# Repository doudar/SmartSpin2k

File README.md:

# You can visit us at [Facebook](https://www.facebook.com/groups/716297469953492/)
# Did you know there's a SmartSpin2k companion App?

Find the source code here! -> [SS2kConfigApp](https://github.com/doudar/SS2kConfigApp/tree/develop) 

You can get it from the Apple App Store here:
<div style="display: flex; flex-wrap: wrap;">

</div>

Or for Android devices: 
<div style="display: flex; flex-wrap: wrap;">

</div>

# About
SmartSpin2k is a DIY project that allows you to turn any spin bike into a smart trainer. With SmartSpin2k, you can connect your spin bike to Zwift, TrainerRoad, or other popular training apps. This allows you to control your bike's resistance automatically, track your performance, and compete with other riders online.

SmartSpin2k is easy to build and requires only a few simple tools. The [entire build process](https://github.com/doudar/SS2k-Hardware/blob/main/SS2kR3BuildingInstructions.pdf) can be completed in under an hour.

If you are looking for a way to turn your spin bike into a smart trainer, SmartSpin2k is the perfect solution. With its new features and improvements, SmartSpin2k rev 3 is the best version yet.

## Getting Started

To get started with SmartSpin2k, you will need the following:

* A spin bike with a resistance control knob.
* A 3D printer.
* A soldering iron and basic soldering skills.

Once you have these materials, you can follow the [these instructions](https://github.com/doudar/SS2k-Hardware/blob/main/SS2kR3BuildingInstructions.pdf) to build your own SmartSpin2k. If you'd prefer to buy a pre-assembled kit, we have them for sale at [SmartSpin2k.com](https://www.smartspin2k.com/purchase-kits) 

## Features

SmartSpin2k offers a number of features, including:

* Automatic incline resistance control: SmartSpin2k can automatically control your bike's resistance based on the resistance settings in your training app. This allows you to focus on your workout and not worry about adjusting the resistance yourself.
* SmartSpin2k ERG function is a great way to improve your cycling performance. It allows you to train at a consistent power output, which is essential for improving your speed and endurance. ERG stands for "electronic resistance control." It works by automatically adjusting the resistance on your bike based on the power output you set in your training app.
* Online competition: SmartSpin2k can connect to Zwift, TrainerRoad, and many other cycling apps allowing you to compete with other riders online. This is a great way to stay motivated and push yourself to new heights.
* Do you have a spin bike that doesn't output realistic or accurate power numbers? If so, you're not alone. Many spin bikes have inaccurate power meters that can make it difficult to track your progress and train effectively. With SmartSpin2k you can calibrate the power output of your spin bike. 

## Conclusion

SmartSpin2k is a great way to turn any spin bike into a smart trainer. With its new features and improvements, SmartSpin2k Rev 3 is the best version yet. If you are looking for a way to improve your indoor cycling experience, SmartSpin2k is the perfect solution.

### Documentation
Everything you need to know is in the [SS2K Wiki](https://github.com/doudar/SmartSpin2k/wiki)
Hardware files and build assets are in [SS2k-Hardware](https://github.com/doudar/SS2k-Hardware).

## Contributing
1. Install Microsoft Visual Code. https://code.visualstudio.com/
2. Install the **pioarduino IDE** extension (`pioarduino.pioarduino-ide`) recommended by this repository in Visual Studio Code.
3. Install Python https://www.python.org/downloads/
4. Install Pre-commit. https://pre-commit.com `py -m pip install pre-commit`
5. Follow any install warnings to add pre-commit to your path. 
6. Install pre-push git hooks: `pre-commit install --hook-type pre-push`
7. Open this project in the pioarduino IDE.

For command-line builds, use a Python virtual environment and run `python -m pip install -r requirements-ci.txt` from the repository root to install the same pinned pioarduino Core used by CI. CI uses Python 3.11. If that environment already has the upstream `platformio` package installed, uninstall it before installing pioarduino; the two packages share Python modules and command names.

pioarduino still uses `platformio.ini`, the `.platformio` tool directory, and the `pio` / `platformio` commands. Build with `pio run -e release` (classic ESP32) or `pio run -e S3release` (ESP32-S3), and run native tests with `pio test -e native`. See [AGENTS.md](AGENTS.md) for build and validation details.

## Important announcement for existing users
If you experience an issue after upgrading firmware, please follow these instructions in the Wiki. Flashing instructions are available [HERE.](https://github.com/doudar/SmartSpin2k/wiki/Loading-Software)

## Licensing
The hardware designs are licensed under the [CERN Open Hardware License Version 2 - Permissive license](https://github.com/doudar/SS2k-Hardware/blob/main/Hardware/LICENSE).
The software in this project is licensed under the [GNU GENERAL PUBLIC LICENSE Version 2, June 1991 license](LICENSE).

[_^^@eMadman's IC4 model_](https://github.com/doudar/SS2k-Hardware/tree/main/Hardware/V2%20-%20Through%20Hole/Direct%20Mount)

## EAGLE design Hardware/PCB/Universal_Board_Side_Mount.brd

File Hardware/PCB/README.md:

PCB files. 

You'll only need these files if you want to customize the PCB or fab it someplace other than pcbway. 

To order directly from PCBway use this link : https://www.pcbway.com/project/shareproject/SmartSpin2k_PCB.html

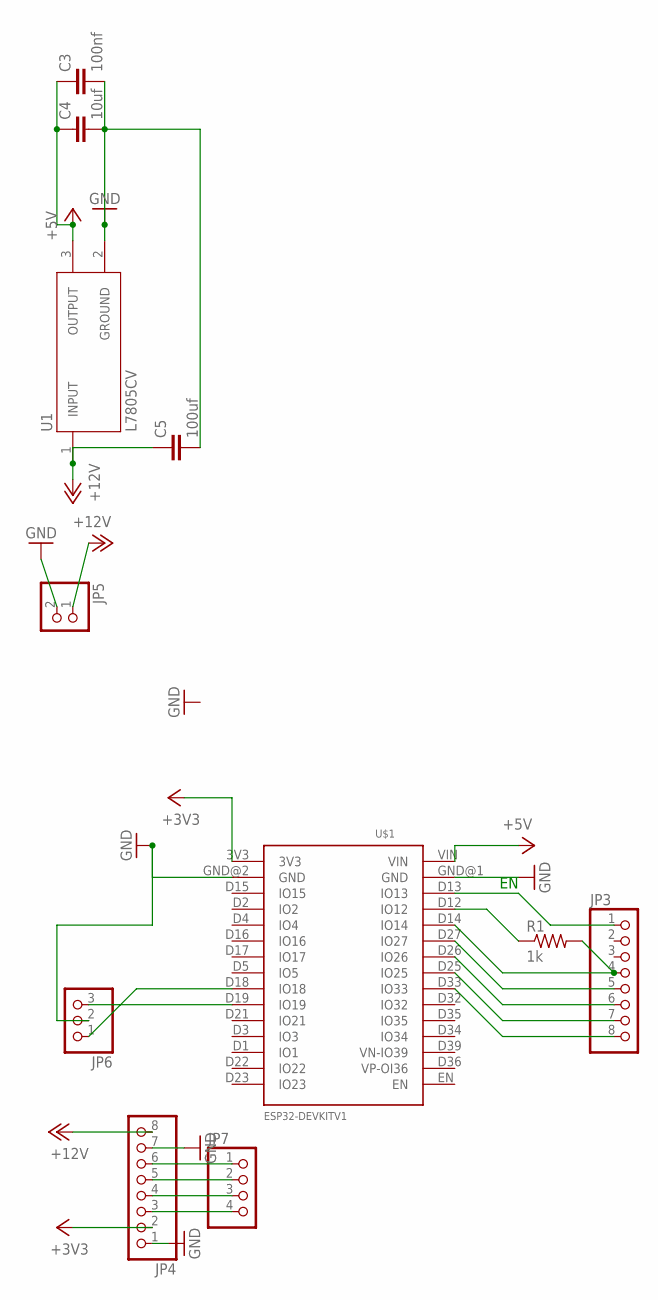
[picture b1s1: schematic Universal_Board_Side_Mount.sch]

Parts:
C3: 100nf; C2.5-3
C4: 10uf; C2.5-3
C5: 100uf; C2.5-3
JP3, JP4: PINHD-1X8; 1X08
JP5: PINHD-1X2; 1X02
JP6: PINHD-1X3; 1X03
JP7: PINHD-1X4; 1X04
R1: 1k; 0204/7
U1: L7805CV; TO255P1040X460X1968-3
U$1: ESP32DEVKITV1; ESP32-DEVKITV1

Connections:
+3V3: JP4.2, U$1.3V3
+5V: C3.1, C4.1, U1.3 (OUTPUT), U$1.VIN
+12V: C5.1, JP4.8, JP5.1, U1.1 (INPUT)
GND: C3.2, C4.2, C5.2, JP4.1, JP4.7, JP5.2, JP6.2, U1.2 (GROUND), U$1.GND@1 (GND), U$1.GND@2 (GND)
unnamed: JP3.4, R1.2, U$1.D14 (IO14)
unnamed: JP3.1, U$1.D13 (IO13)
unnamed: R1.1, U$1.D12 (IO12)
unnamed: JP3.5, U$1.D27 (IO27)
unnamed: JP3.6, U$1.D26 (IO26)
unnamed: JP3.7, U$1.D25 (IO25)
unnamed: JP3.8, U$1.D33 (IO33)
unnamed: JP4.6, JP7.1
unnamed: JP4.5, JP7.2
unnamed: JP4.4, JP7.3
unnamed: JP4.3, JP7.4
unnamed: JP6.3, U$1.D19 (IO19)
unnamed: JP6.1, U$1.D18 (IO18)

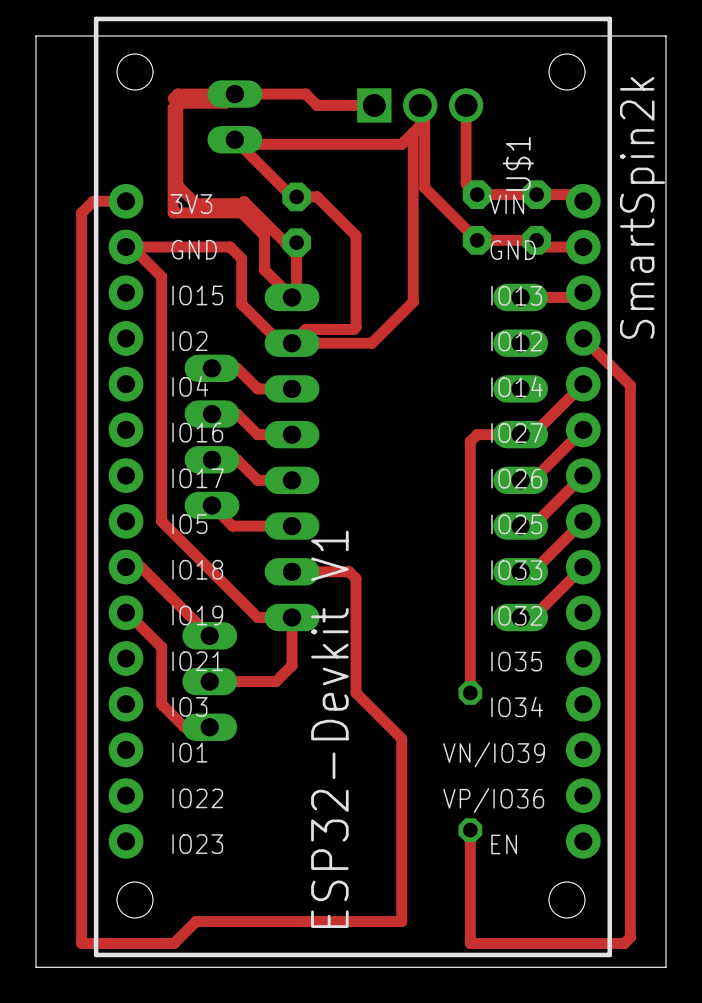
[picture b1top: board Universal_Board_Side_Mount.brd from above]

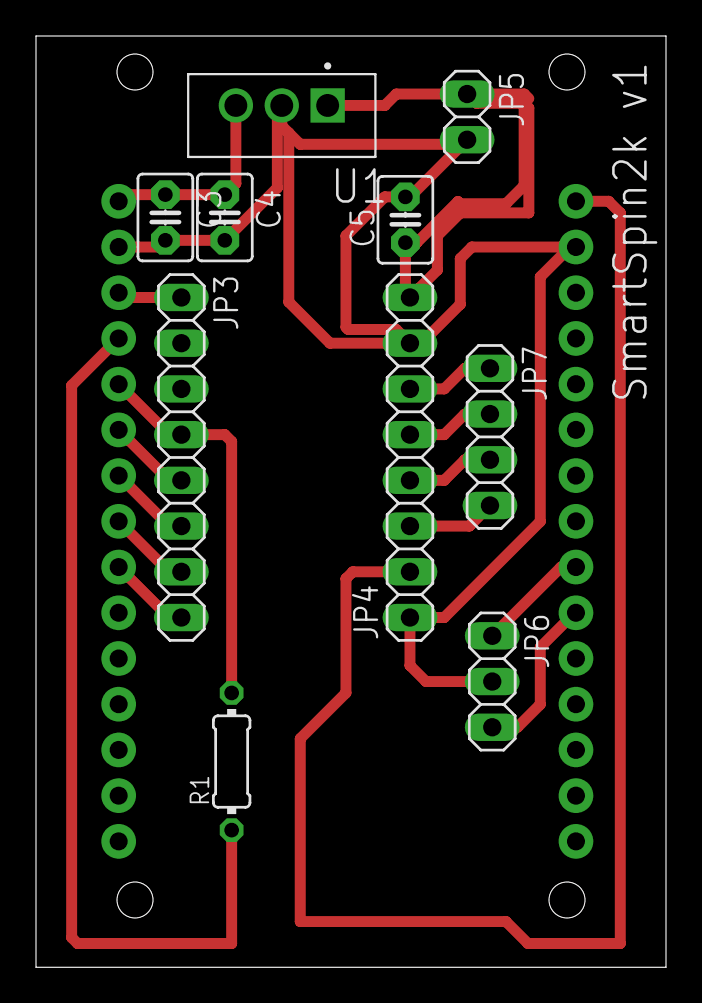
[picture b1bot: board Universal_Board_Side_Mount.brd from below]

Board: 2 copper layers, 35.0 x 51.7 mm, 11 parts (10 on the bottom side), 17 nets.

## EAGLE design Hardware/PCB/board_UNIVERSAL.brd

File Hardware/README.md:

# SmartSpin2k Hardware
V3 is the brand spanking new version where we've gone to a more rigid mount and designed a completly custom PCB with SMT components which can be manufactured using automated techniques. The newest PCB sports a uart->serial driver to allow direct communication with Peloton bikes. 

V2 prints easier, is smaller and uses less hardware. It has a much better gear ratio than V1 and supports a carrier board PCB onto which the devkits mount for easy wiring/soldering.  A rigid mount referred to as Direct Mount is available for stable mounting.

V1 is the oldest printable version. It's slightly more sophisticated than duct tape and cardboard. The common assets do not work with this version, the V1 folder includes knob cups and adaptors specific to V1. You'll probably only use this directory if you need to print replacement parts for a V1.

Hardware is available in two primary versions.  V2 - The Through-Hole soldered version, can easily be DIY'ed by anyone with basic soldering and electronics experience.  V3 - Integrated PCB is new and uses a manufactured PCB with a serial interface specifically designed for integration with Peloton bikes.  

There's additional information in each folder to help you determine what parts might work best for you. 

# Directories
## [V2 - Through-Hole Soldered](https://github.com/doudar/SS2k-Hardware/tree/main/Hardware/V2%20-%20Through%20Hole)
Available in many case versions.  The direct mount mod is the recommended solution for new builders and DIYers.  It is supported on various bikes and is easily adapted to other form factors.  

## [V3 - Integrated PCB](https://github.com/doudar/SS2k-Hardware/tree/main/Hardware/V3%20-%20Integrated%20PCB)
Use with the SMT manufaactured PCB and for compatibility with Peloton bikes.

## [Common Assets](https://github.com/doudar/SS2k-Hardware/tree/main/Hardware/Common%20Assets)
### [Arm](https://github.com/doudar/SS2k-Hardware/tree/main/Hardware/Common%20Assets/Arm)
The Arm is used to connect the SmartSpin2k to the bike mount.  See Readme for sizing and fitment information.

Required for V3 and V2 Direct Mount.

### [Bike Mount](https://github.com/doudar/SS2k-Hardware/tree/main/Hardware/Common%20Assets/Bike%20Mount)
Attaches to the head tube of your bike and provides an attachment point for the arm.

Required for V3 and V2 Direct Mount

### [Gears](https://github.com/doudar/SS2k-Hardware/tree/main/Hardware/Common%20Assets/Gears)
Internal drive gears for the SmartSpin2k.  11:40t gearing.

Required for all V2 and V3 variations

### [Inserts](https://github.com/doudar/SS2k-Hardware/tree/main/Hardware/Common%20Assets/Inserts)
Choose the appropriate insert for your bike.  There are some generic knob designs that apply to several no-name models.  Browse the directory - your bike may already be covered.

Required for all V2 and V3 variations

### [KnobCup](https://github.com/doudar/SS2k-Hardware/tree/main/Hardware/Common%20Assets/KnobCups)
Knob Cup retains the insert and connects to the internal gearbox of the SmartSpin2k

Required for all V2 and V3 variations

### [Shifters](https://github.com/doudar/SS2k-Hardware/tree/main/Hardware/Common%20Assets/Shifters)
You'll want shifters to do sim rides with.  Print this in TPU.

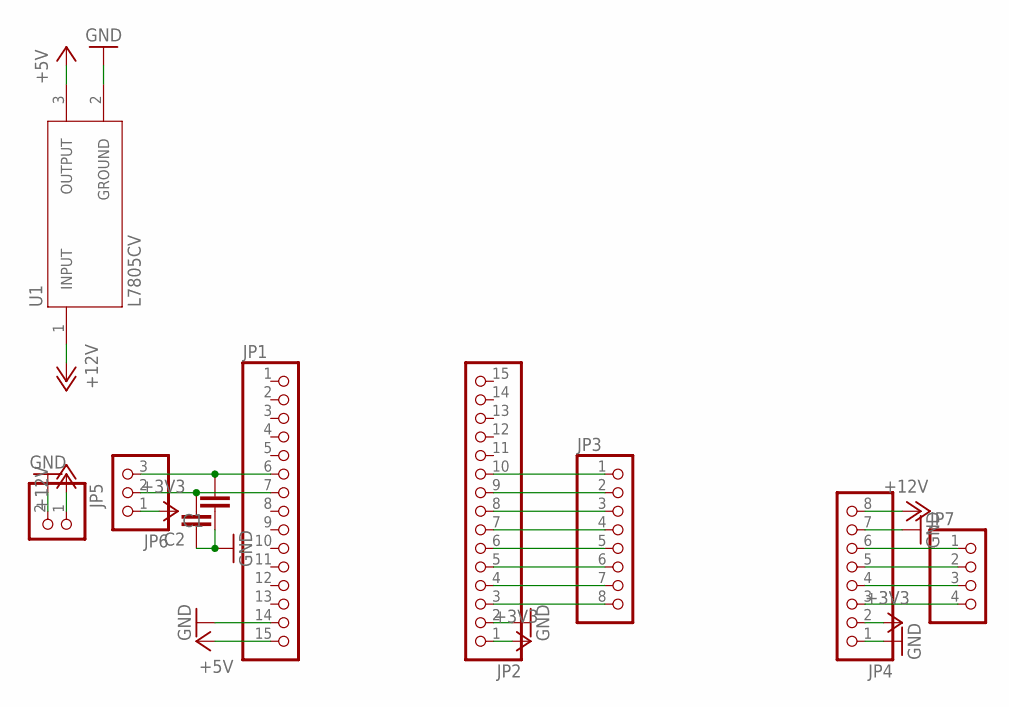
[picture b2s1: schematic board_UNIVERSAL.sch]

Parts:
C1, C2: C-EU025-030X050; C025-030X050
JP1, JP2: PINHD-1X15; 1X15
JP3, JP4: PINHD-1X8; 1X08
JP5: PINHD-1X2; 1X02
JP6: PINHD-1X3; 1X03
JP7: PINHD-1X4; 1X04
U1: L7805CV; TO255P1040X460X1968-3

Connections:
+3V3: JP2.1, JP4.2, JP6.1
+5V: JP1.15, U1.3 (OUTPUT)
+12V: JP4.8, JP5.1, U1.1 (INPUT)
GND: C1.1, C2.1, JP1.14, JP2.2, JP4.1, JP4.7, JP5.2, U1.2 (GROUND)
unnamed: C2.2, JP1.7, JP6.2
unnamed: C1.2, JP1.6, JP6.3
unnamed: JP2.10, JP3.1
unnamed: JP2.8, JP3.3
unnamed: JP2.7, JP3.4
unnamed: JP2.6, JP3.5
unnamed: JP2.9, JP3.2
unnamed: JP4.6, JP7.1
unnamed: JP4.5, JP7.2
unnamed: JP4.4, JP7.3
unnamed: JP4.3, JP7.4
unnamed: JP2.5, JP3.6
unnamed: JP2.4, JP3.7
unnamed: JP2.3, JP3.8

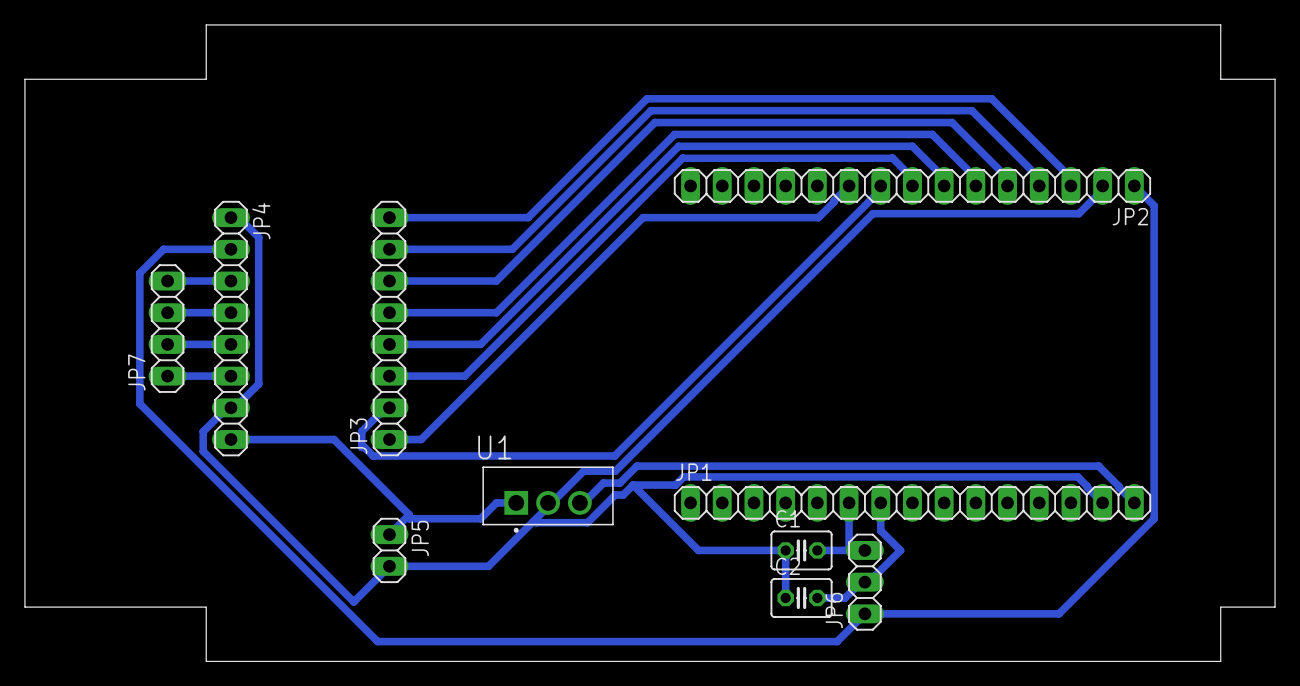
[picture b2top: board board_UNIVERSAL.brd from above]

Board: 2 copper layers, 100.2 x 51.0 mm, 10 parts (0 on the bottom side), 18 nets.

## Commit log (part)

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2025-11-18 Initial plan
2025-11-18 Fix misleading comments on resistance level conversion logic
2025-11-18 Added fallback to ERG while in resistance mode if we have no position information.
2025-11-18 comments and changelog updated.
2025-11-18 tweaked response in Resistance Mode
2025-11-20 Bump actions/checkout from 5 to 6
    Bumps [actions/checkout](https://github.com/actions/checkout) from 5 to 6.
    - [Release notes](https://github.com/actions/checkout/releases)
    - [Changelog](https://github.com/actions/checkout/blob/main/CHANGELOG.md)
    - [Commits](https://github.com/actions/checkout/compare/v5...v6)
    ---
    updated-dependencies:
2025-11-21 Fix spin down calibration by using indicate() for FTMS Control Point responses
    According to FTMS 1.0 spec, Control Point responses MUST use BLE indication (with acknowledgment) not notification (without acknowledgment). This fixes Zwift not recognizing spin down calibration com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
2025-11-21 Complete fix for spin down calibration issue - all checks passed
2025-11-21 Make Zwift happy during spin down by sending "stop pedaling" every 1 second
2025-11-24 Add power scalers for stepper hold and homing; update driver settings for improved stall detection
2025-11-24 Cadence needs to be >5 to initiate homing.
2025-11-24 added ftms homing user abort
2025-11-24 Minor text changes
2025-11-24 divide by 4 for resistance homing
2025-12-01 require cadence for 2 seconds before homing
2025-12-01 reduced delay to power down.
2025-12-02 More homing refinements
2025-12-03 Update links card
2025-12-11 Update CHANGELOG.md
    links card update
2025-12-11 Add custom characteristic command processing to WebSocket server
2025-12-11 Update documentation for WebSocket custom characteristic support
2025-12-11 Bump actions/cache from 4 to 5
    Bumps [actions/cache](https://github.com/actions/cache) from 4 to 5.
    - [Release notes](https://github.com/actions/cache/releases)
    - [Changelog](https://github.com/actions/cache/blob/main/RELEASES.md)
    - [Commits](https://github.com/actions/cache/compare/v4...v5)
    ---
    updated-dependencies:
2025-12-11 Send custom characteristic responses back through WebSocket
2025-12-11 added include for websocket appender
2025-12-17 Fix for Zwift On Android.
2025-12-18 IC4 reported HR won't override other HRM.
2025-12-18 Improved ERG response for homed tables.
2025-12-18 updated default settings
2025-12-25 - Removed >0 watts requirement to compute ERG.
2025-12-26 Add inactivity timeout config
2025-12-27 initial
2025-12-27 a little better
2025-12-28 almost there
2025-12-28 sync or async?
2025-12-28 bugfixes
2025-12-30 Working with Mark Roy to tune PID
2025-12-30 Use minutes instead of ms. Fix BLE
2025-12-30 Remove obsolete ms convertions
2025-12-31 - More ERG tweaks for Marc Roy.
2025-12-31 Revert "- More ERG tweaks for Marc Roy."
    This reverts commit ae53db69d04b5b06ce3ca93ab1a85a3d2c8b28c0.
2025-12-31 Merged Mark Roy with Marc Roy
2025-12-31 ERG being decoded correctly.
2025-12-31 Cleaning up
2025-12-31 - Added feed forward, disabled PowerTable for ERG lookup.
2026-01-01 Added tests and removal of duplicates in pt column.
2026-01-02 cleanup
2026-01-02 Set gear 8 after startup homing
2026-01-02 After startup homing, set gear 8.
2026-01-02 experimental lookup methods
2026-01-03 before removing monotonicity in favor of regression
2026-01-04 Ready to test again.
2026-01-04 added y-axis lock to testing
2026-01-04 Load power table if not yet loaded during session
2026-01-05 working great. needs cleanup.
2026-01-10 testing complete
2026-01-10 Switched inactivity timeout to 2F for compatibility with other recent changes.
2026-01-10 Fixed Case break from merge.
2026-01-10 Add BLE log streaming implementation
2026-01-10 Fix VLA stack overflow risk and revert unrelated dependencies.lock changes
2026-01-10 Change BLE_BLELogging characteristic code from 0x2F to 0x30
2026-01-10 Use existing BLE notification function instead of custom implementation
2026-01-11 hw test updates
2026-01-11 an example of why hardware should be seperate from software
2026-01-12 Updated case
2026-01-19 Increase BLE message size and silence MTU log
    Raised MAX_MESSAGE_SIZE in BleAppender from 180 to 500 to support larger BLE messages. Commented out the MTU update log in BLE_Server.cpp to reduce log verbosity.
2026-01-19 Fix ERG mode logic and improve power table validation; reset target incline on stop
2026-01-22 Include connected devices in BLE scan results
    Updated BLE scan logic to add connected devices to the found devices list when using the 'ANY' wildcard. Refactored scan end callback to remove redundant device aggregation, as devices are now added 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
2026-01-23 Sole Sb1200
2026-01-24 logging improvements
2026-01-31 fixed ERG sensitivity not being decimal in app
2026-01-31 Added Schwinn ACparts
2026-02-06 Removed initial connection params
2026-02-17 Update style.css
    accordion sections
2026-02-17 Update settings.html
    accordion sections
2026-02-17 Update CHANGELOG.md
    accordion sections
2026-03-01 updated connection params
2026-03-01 Add BLE appender and enhance logging for target positions
2026-03-01 Add Zwift custom BLE service and integrate virtual shifting functionality
2026-03-03 Controls almost working.
2026-03-03 Zwift rxing commands
2026-03-03 eliminated shifting feedback loop
2026-03-08 in progress
2026-03-08 Enhance DirCon service registration and write handling; remove deprecated methods
2026-03-08 Refactor BLE_Zwift_Service to improve session management and logging; remove handshake state handling
2026-03-09 back to Arduino BLE library
2026-03-09 Refactor BLE_Zwift_Service for improved code readability and consistency; adjust spacing and update service UUID references
2026-03-09 Thread safety and advertisement cleanup
2026-03-12 Enhance BLE_Zwift_Service with new payload handling methods and update command codes for trainer configuration
2026-03-12 Fixed some ZP errors
2026-03-18 updated countersink holes
2026-03-19 templated a couple functions
2026-03-19 Updated vents
2026-03-22 Case updates
2026-04-05 Update CA certificate for raw.githubusercontent.com
    - Replaced the outdated Sectigo certificate with the new Let's Encrypt R12 certificate.
    - Updated the last modified date to 2026-04-05.
2026-04-05 Debug working for S3
2026-04-11 [skip actions] changed readme to use the banner in hardware
2026-04-15 added openBikeControl
2026-04-21 working
2026-04-22 TMC driver work
2026-04-23 All go
2026-04-29 updated platformio.ini
2026-04-30 Better homing
2026-04-30 3 taps if first two don't agree
2026-04-30 Coolstep off during homing
2026-05-01 Garmin BLE changes
2026-05-02 fix(ble): restructure advertising and ensure spec compliance for Garmin compatibility
    - Restructured BLE advertising to prioritize the Cycling Power Service (CPS) UUID (0x1818) in the primary packet, mimicking commercial power meters to bypass strict Garmin discovery filters.
    - Added BLE Appearance (0x0484) to explicitly identify the device as a Cycling Power Sensor.
    - Moved the SmartSpin2k custom service UUID to the scan response to prevent advertising packet overflow and reduce noise for central scanners.
    - Updated the Cycling Power Measurement characteristic to NOTIFY only to comply with the Bluetooth CPP v1.1 specification.
    - Forced a public MAC address type to ensure stable pairing with
2026-05-02 updated changelog.md. Moved constants and definitions to header file. Code cleanup
2026-05-02 removed unused _closeToTarget
2026-05-02 added additional position update.
2026-05-02 formatting
2026-05-02 updated changelog
2026-05-02 fixed advertising
2026-05-03 Disabled OpenBikeControl and ZP (for now)
2026-05-04 Advertisement work
2026-05-04 removed hrm from advertisement
2026-05-04 updated build.yml
2026-05-06 [skip actions] Added better sunny 1805 pictures. Aligned sdkconfig.debug with release
2026-05-11 Guard networking when WiFi is disabled
    Agent-Logs-Url: https://github.com/doudar/SmartSpin2k/sessions/931c8bb8-5824-4b5e-b080-084036fdcd3d
2026-05-11 Deduplicate WiFi shutdown handling
    Agent-Logs-Url: https://github.com/doudar/SmartSpin2k/sessions/931c8bb8-5824-4b5e-b080-084036fdcd3d
2026-05-12 Move networking guards into main
    Agent-Logs-Url: https://github.com/doudar/SmartSpin2k/sessions/e759c192-9c60-4e03-be5d-88fac969b873
2026-05-12 Extract centralized network startup helper
    Agent-Logs-Url: https://github.com/doudar/SmartSpin2k/sessions/e759c192-9c60-4e03-be5d-88fac969b873
2026-05-12 Switch zero-watt ERG targets to sim mode
    Agent-Logs-Url: https://github.com/doudar/SmartSpin2k/sessions/33f20c65-9299-4587-81af-67f21f7b2a65
2026-05-12 Inline zero-watt ERG check
    Agent-Logs-Url: https://github.com/doudar/SmartSpin2k/sessions/760e2bb2-08f2-4f1e-b692-ec66f9a3726b
2026-05-22 sleep after 15min of inactivity after reboot
2026-05-23 changelog
2026-05-26 Added constants for namespace and keys and unwrapped the setup for readability.
2026-05-27 Add agent notes for SmartSpin2k firmware
2026-05-27 Simplified logic further. Moved flag from NVS to RTC memory.
2026-05-29 initial_commit
2026-06-18 build fix
2026-06-24 Bump dorny/paths-filter from 3 to 4
    Bumps [dorny/paths-filter](https://github.com/dorny/paths-filter) from 3 to 4.
    - [Release notes](https://github.com/dorny/paths-filter/releases)
    - [Changelog](https://github.com/dorny/paths-filter/blob/master/CHANGELOG.md)
    - [Commits](https://github.com/dorny/paths-filter/compare/v3...v4)
    ---
    updated-dependencies:
2026-06-24 Bump actions/upload-artifact from 5 to 7
    Bumps [actions/upload-artifact](https://github.com/actions/upload-artifact) from 5 to 7.
    - [Release notes](https://github.com/actions/upload-artifact/releases)
    - [Commits](https://github.com/actions/upload-artifact/compare/v5...v7)
    ---
    updated-dependencies:
    - dependency-name: actions/upload-artifact
2026-06-24 Bump dangoslen/changelog-enforcer from 3.6.1 to 3.7.0
    Bumps [dangoslen/changelog-enforcer](https://github.com/dangoslen/changelog-enforcer) from 3.6.1 to 3.7.0.
    - [Release notes](https://github.com/dangoslen/changelog-enforcer/releases)
    - [Changelog](https://github.com/dangoslen/changelog-enforcer/blob/main/CHANGELOG.md)
    - [Commits](https://github.com/dangoslen/changelog-enforcer/compare/v3.6.1...v3.7.0)
    ---
    updated-dependencies:
2026-06-24 Bump softprops/action-gh-release from 2 to 3
    Bumps [softprops/action-gh-release](https://github.com/softprops/action-gh-release) from 2 to 3.
    - [Release notes](https://github.com/softprops/action-gh-release/releases)
    - [Changelog](https://github.com/softprops/action-gh-release/blob/master/CHANGELOG.md)
    - [Commits](https://github.com/softprops/action-gh-release/compare/v2...v3)
    ---
    updated-dependencies:
2026-06-24 Bump actions/checkout from 6 to 7
    Bumps [actions/checkout](https://github.com/actions/checkout) from 6 to 7.
    - [Release notes](https://github.com/actions/checkout/releases)
    - [Changelog](https://github.com/actions/checkout/blob/main/CHANGELOG.md)
    - [Commits](https://github.com/actions/checkout/compare/v6...v7)
    ---
    updated-dependencies:
2026-06-24 Bump actions/download-artifact from 6 to 8
    Bumps [actions/download-artifact](https://github.com/actions/download-artifact) from 6 to 8.
    - [Release notes](https://github.com/actions/download-artifact/releases)
    - [Commits](https://github.com/actions/download-artifact/compare/v6...v8)
    ---
    updated-dependencies:
    - dependency-name: actions/download-artifact
2026-06-25 initial changes
    Custom BLE handling for Spinning CHrono Power
2026-06-25 feat: add ChronoData sensor support and implement BLE client task management
